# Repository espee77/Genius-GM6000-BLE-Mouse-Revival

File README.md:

# Reviving a Classic: Genius GM-6000 Wireless BLE / Wired USB / Air Mouse Conversion

This project is an open-source hardware and firmware conversion for the classic Genius GM-6000 mechanical ball mouse.

## History

Introduced in the late 1980s, the Genius GM-6000 was one of the flagship serial mice from [KYE Systems](https://www.geniusnet.com/en) under its Genius brand. At a time when the computer mouse was becoming an essential PC peripheral, the [Genius GM-6000](http://www.tcocd.de/Pictures/Peripheral/Genius/Genius.shtml) stood out with its robust optomechanical design, dynamic resolution technology, and support for both Microsoft and Mouse Systems serial protocols. Bundled with graphics software including Menu Maker and Dr. Halo/Dr. Genius, it was marketed as a premium mouse for both business and graphics applications.

By 1989, Genius advertisements described the company as "the largest selling mouse in Europe," with the GM-6000 featured prominently in its international marketing campaigns. Contemporary reviews also praised the mouse for its accuracy, compatibility, and comprehensive software bundle.

More than three decades later, the GM-6000 is still appreciated by collectors and retro-computing enthusiasts for its solid construction and durable mechanical tracking system. This project preserves those original mechanics while replacing the obsolete electronics with modern Bluetooth Low Energy technology, a rechargeable battery, and optional Air Mouse functionality.

---

## The Goal

The goal of this project is to preserve the look, feel, and mechanics of the original Genius GM-6000 while replacing its obsolete electronics with a modern Bluetooth Low Energy (BLE) system and adding Air Mouse functionality.

Instead of replacing the original ball mechanism with a modern optical sensor, this project preserves the original encoder wheels and tracking mechanics. A custom infrared optical detection system using IR LEDs and phototransistors reads the original quadrature encoders, maintaining the unique feel and behavior of the original mouse.

At the heart of the conversion is a custom PCB based on the [**Seeed Studio XIAO nRF52840 Sense**](https://wiki.seeedstudio.com/XIAO_BLE/), providing Bluetooth LE connectivity, rechargeable Li-Po battery support, intelligent power management, and modern firmware—all while fitting completely inside the original mouse shell.

If this project inspires someone to restore vintage hardware, learn electronics, or build an even better version, then it has already achieved its goal. Contributions, suggestions, forks, and improvements are always welcome.

---

# Project Goals

* Preserve the original appearance of the mouse
* Preserve the original ball and encoder mechanics
* Replace the original electronics with a modern custom PCB
* Add wireless Bluetooth Low Energy (BLE) connectivity
* Integrate a rechargeable Li-Po battery
* Keep both hardware and firmware fully open source

---

# Features

## Ball Mouse

* Bluetooth Low Energy (BLE) HID and wired USB HID support
* Original mechanical ball tracking
* Original infrared quadrature encoder system
* Adjustable cursor speed
* Three original mouse buttons
* Hold the middle button while moving the mouse to scroll smoothly
* Independent sensitivity settings for BLE and USB modes

## Air Mouse

* Automatic Air Mouse mode in both BLE and USB operation
* Automatic switching based on mouse orientation
* Motion smoothing, tremor reduction, and spike filtering
* Full button support while in Air Mouse mode

## Bluetooth

* Compatible with Windows, macOS, Linux, Android, and iPadOS
* Automatic BLE reconnection
* Bluetooth Battery Service (battery level reporting)
* Optimized BLE connection parameters for responsive cursor movement

## Power Management

* Rechargeable Li-Po battery
* Intelligent multi-stage power management
* Automatic IR LED power control
* Light Sleep and Deep Sleep modes for maximum battery life
* Automatic wake-up from movement, IMU motion (during Light Sleep), or button press (from Deep Sleep)

## Hardware

* Custom PCB designed specifically for the GM-6000
* Based on the Seeed Studio XIAO nRF52840 Sense
* Preserves the original buttons and tracking hardware
* Compact design that fits completely inside the original enclosure

---

# Using the Mouse

Despite its modern electronics, the converted GM-6000 is designed to preserve the familiar feel of the original mouse while adding modern wireless features and intelligent power management.

## Ball Mouse

The original mechanical ball, encoder wheels, and tracking mechanism are fully preserved. Cursor movement is generated from the original quadrature encoders, maintaining the characteristic feel of the original GM-6000.

## Scrolling

Since the original mouse has no scroll wheel, scrolling is performed by holding the **middle mouse button** while moving the mouse forward or backward. This allows smooth scrolling without altering the mouse's original appearance.

## Air Mouse

Rotating the mouse onto its side automatically activates **Air Mouse Mode**. The built-in IMU controls the cursor, making the mouse suitable for presentations or media control.

Switching between Ball Mouse and Air Mouse modes is completely automatic—no switches or software are required.

## USB & Bluetooth

The mouse operates as both a wired USB mouse and a Bluetooth Low Energy mouse. Connecting a USB cable automatically enables wired operation, while disconnecting it returns the mouse to Bluetooth mode.

## Intelligent Sleep Modes

To maximize battery life, the firmware automatically manages power consumption.

| Mode | Description |
|------|-------------|
| **Active** | Full performance while the mouse is in use. |
| **Light Sleep** | Infrared tracking is powered down while remaining ready to wake almost instantly. |
| **Deep Sleep** | Bluetooth disconnects and the mouse enters its lowest power state. |

The mouse automatically wakes from movement, IMU motion (during Light Sleep), or a button press (from Deep Sleep).

## Battery

Battery level is continuously monitored and reported through the Bluetooth Battery Service, allowing supported operating systems to display the remaining battery percentage.

## Factory Reset

If you experience Bluetooth pairing or connection problems, the firmware includes a built-in **Factory Reset** function.

With the mouse powered off, press and hold the **left**, **middle**, and **right** mouse buttons simultaneously while turning the mouse on. Keep all three buttons pressed for approximately **5 seconds** until the status LEDs indicate that the reset has started. The mouse will erase all stored Bluetooth pairing information, saved settings, usage statistics, battery statistics, and internal storage before automatically rebooting.

After a Factory Reset, remove the mouse from your computer's Bluetooth device list (if previously paired) and pair it again as a new device.

---

# Repository Contents

* [Firmware Installation Manual](Firmware%20installation%20manual.md)
* [Bill of material](https://github.com/espee77/Genius-GM6000-BLE-Mouse-Revival/blob/main/V1.0/Bill%20of%20Materials%20(BOM))
* [KiCad 10 project files](https://github.com/espee77/Genius-GM6000-BLE-Mouse-Revival/tree/main/V1.0/KICAD)
* [Schematics](https://github.com/espee77/Genius-GM6000-BLE-Mouse-Revival/tree/main/V1.0/Schematic)
* [Datasheets](https://github.com/espee77/Genius-GM6000-BLE-Mouse-Revival/tree/main/V1.0/Datasheets)
* [Firmware source code](https://github.com/espee77/Genius-GM6000-BLE-Mouse-Revival/tree/main/V1.01/Firmware)
* [JLCPCB zip file for board ordering](https://github.com/espee77/Genius-GM6000-BLE-Mouse-Revival/tree/main/V1.0/JLCPCB)
* [3D CAD files](https://github.com/espee77/Genius-GM6000-BLE-Mouse-Revival/tree/main/V1.0/3D%20files/Step214)
* [Pictures with assembly notes](https://github.com/espee77/Genius-GM6000-BLE-Mouse-Revival/tree/main/V1.0/Pictures%20with%20assembly%20notes)

---

# Why Open Source?

This project started as a fun way to combine retro hardware with modern electronics while preserving a classic piece of computer history.

By making both the hardware and firmware open source, I hope others can learn from it, improve the design, or use it as the foundation for their own retro hardware projects.

Contributions are always welcome, whether they involve hardware improvements, firmware development, documentation, testing, or entirely new ideas.

---

# Current Status

- **[V1.0 – Stable Release](https://github.com/espee77/Genius-GM6000-BLE-Mouse-Revival/tree/main/V1.01)**
- Second-generation custom PCB completed
- Stable Bluetooth Low Energy (BLE) HID firmware
- Reliable deep-sleep wake and automatic BLE reconnection
- Ball Mouse mode fully functional
- Air Mouse mode fully functional
- USB wired mouse mode implemented
- Battery monitoring and charging support
- Automatic power management with multi-stage sleep modes
- Built-in Factory Reset and diagnostic tools
- Extensively tested in daily use
- Optimized Bluetooth performance, responsiveness, and power consumption

---

# Disclaimers

* This is an experimental hobby project.
* Use the provided files and information entirely at your own risk.
* Li-Po batteries and electronic modifications can be hazardous if handled improperly. Always follow appropriate safety precautions.
* This hardware will not fit the Genius GM-6 which differs slightly from the GM-6000 (encoder positions, contact roller size, and rear switch).

---

# Acknowledgements

This project is an independent, community-created restoration effort. The CAD models were created by measuring an original Genius GM-6000 mouse and are not based on or derived from original manufacturer CAD data. "Genius" is a trademark of its respective owner and is used solely to identify the compatible product.
Special thanks to the retro hardware, maker, and open-source communities whose shared knowledge, documentation, and projects made this conversion possible.

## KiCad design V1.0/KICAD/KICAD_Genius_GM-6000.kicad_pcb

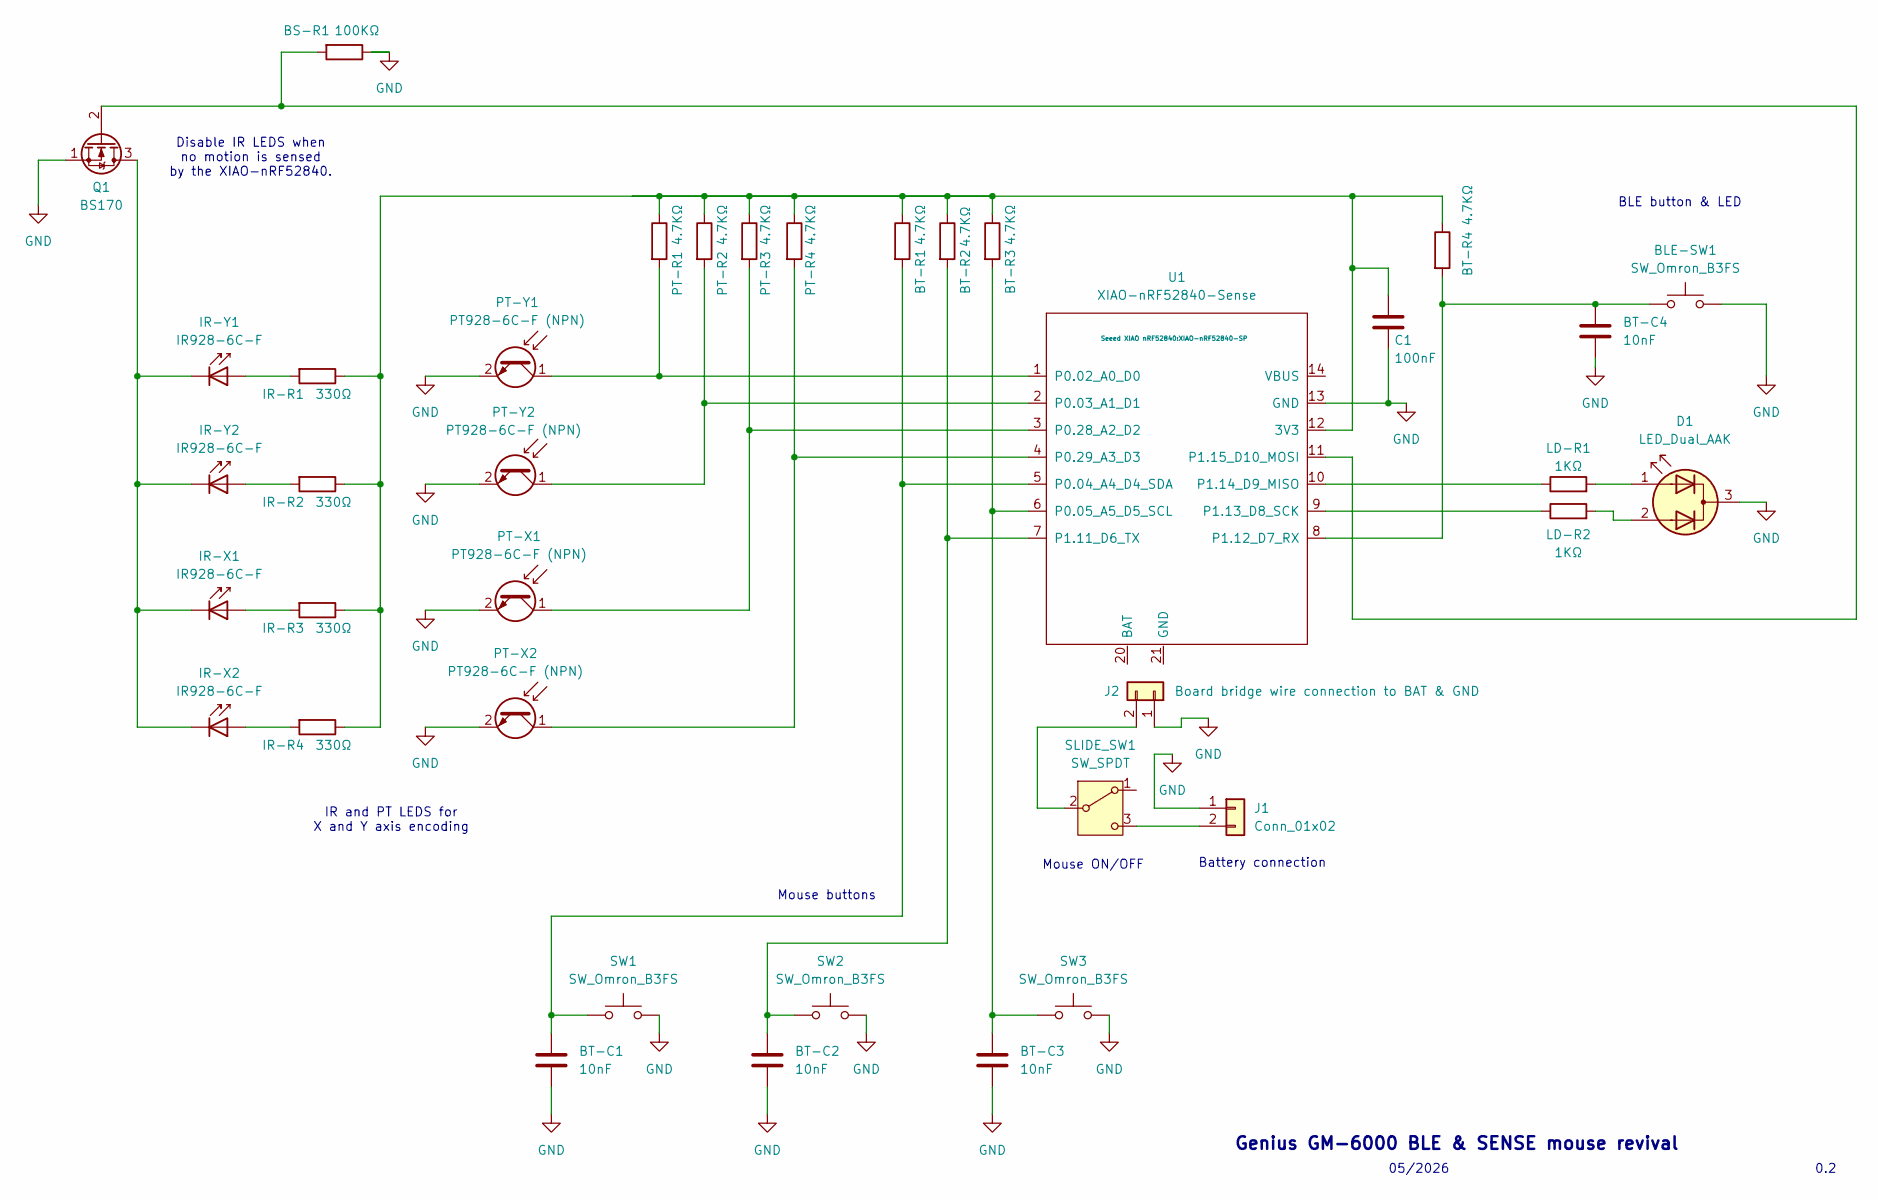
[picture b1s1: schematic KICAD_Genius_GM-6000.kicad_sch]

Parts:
BLE-SW1: SW_Omron_B3FS; SW_PUSH_6mm
BS-R1: 100KΩ; R_Axial_DIN0207_L6.3mm_D2.5mm_P7.62mm_Horizontal
BT-C1, BT-C2, BT-C3, BT-C4: 10nF; C_Disc_D5.0mm_W2.5mm_P2.50mm
BT-R1, BT-R2, BT-R3, BT-R4: 4.7KΩ; R_Axial_DIN0207_L6.3mm_D2.5mm_P7.62mm_Horizontal
C1: 100nF; C_Disc_D5.0mm_W2.5mm_P2.50mm
D1: LED_Dual_AAK; LED_D3.0mm-3
IR-R1, IR-R2, IR-R3, IR-R4: 330Ω; R_Axial_DIN0207_L6.3mm_D2.5mm_P7.62mm_Horizontal
IR-X1, IR-X2: IR928-6C-F; LED_SideEmitter_Rectangular_W4.5mm_H1.6mm
IR-Y1, IR-Y2: IR928-6C-F; LED_SideEmitter_Rectangular_W4.5mm_H1.6mm
J1: Conn_01x02
J2: Board bridge wire connection to BAT & GND; PinHeader_1x02_P2.54mm_Vertical
LD-R1, LD-R2: 1KΩ; R_Axial_DIN0207_L6.3mm_D2.5mm_P7.62mm_Horizontal
PT-R1, PT-R2, PT-R3, PT-R4: 4.7KΩ; R_Axial_DIN0207_L6.3mm_D2.5mm_P7.62mm_Horizontal
PT-X1, PT-X2: PT928-6C-F (NPN); Osram_LPT80A
PT-Y1, PT-Y2: PT928-6C-F (NPN); Osram_LPT80A
Q1: BS170; TO-92L_Inline_Wide
SLIDE_SW1: SW_SPDT; SW_Slide_SPDT_Straight_CK_OS102011MS2Q
SW1, SW2, SW3: SW_Omron_B3FS; SW_PUSH_6mm
U1: XIAO-nRF52840-Sense; XIAO-nRF52840-SP

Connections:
GND: BLE-SW1.2, BS-R1.1, BT-C1.2, BT-C2.2, BT-C3.2, BT-C4.2, C1.2, D1.3 (K), J1.1, J2.1, PT-X1.2 (E), PT-X2.2 (E), PT-Y1.2 (E), PT-Y2.2 (E), Q1.1 (S), SW1.2, SW2.2, SW3.2, U1.13 (GND)
unnamed: D1.1 (A1), LD-R1.2
unnamed: D1.2 (A2), LD-R2.2
unnamed: IR-R3.2, IR-X1.2 (A)
unnamed: IR-X1.1 (K), IR-X2.1 (K), IR-Y1.1 (K), IR-Y2.1 (K), Q1.3 (D)
unnamed: IR-R4.2, IR-X2.2 (A)
unnamed: IR-R1.2, IR-Y1.2 (A)
unnamed: IR-R2.2, IR-Y2.2 (A)
unnamed: J1.2, SLIDE_SW1.3 (C)
unnamed: J2.2, SLIDE_SW1.2 (B)
unnamed: PT-R3.2, PT-X1.1 (C), U1.3 (P0.28_A2_D2)
unnamed: PT-R4.2, PT-X2.1 (C), U1.4 (P0.29_A3_D3)
unnamed: PT-R1.2, PT-Y1.1 (C), U1.1 (P0.02_A0_D0)
unnamed: PT-R2.2, PT-Y2.1 (C), U1.2 (P0.03_A1_D1)
unnamed: BS-R1.2, Q1.2 (G), U1.11 (P1.15_D10_MOSI)
unnamed: BT-R1.1, BT-R2.1, BT-R3.1, BT-R4.1, C1.1, IR-R1.1, IR-R2.1, IR-R3.1, IR-R4.1, PT-R1.1, PT-R2.1, PT-R3.1, PT-R4.1, U1.12 (3V3)
unnamed: BT-C1.1, BT-R1.2, SW1.1, U1.5 (P0.04_A4_D4_SDA)
unnamed: BT-C3.1, BT-R3.2, SW3.1, U1.6 (P0.05_A5_D5_SCL)
unnamed: BT-C2.1, BT-R2.2, SW2.1, U1.7 (P1.11_D6_TX)
unnamed: BLE-SW1.1, BT-C4.1, BT-R4.2, U1.8 (P1.12_D7_RX)
unnamed: LD-R2.1, U1.9 (P1.13_D8_SCK)
unnamed: LD-R1.1, U1.10 (P1.14_D9_MISO)

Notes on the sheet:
0.2
Battery connection
Mouse buttons
IR and PT LEDS for X and Y axis encoding
05/2026
Mouse ON/OFF
Genius GM-6000 BLE & SENSE mouse revival
Disable IR LEDS when no motion is sensed by the XIAO-nRF52840.
BLE button & LED

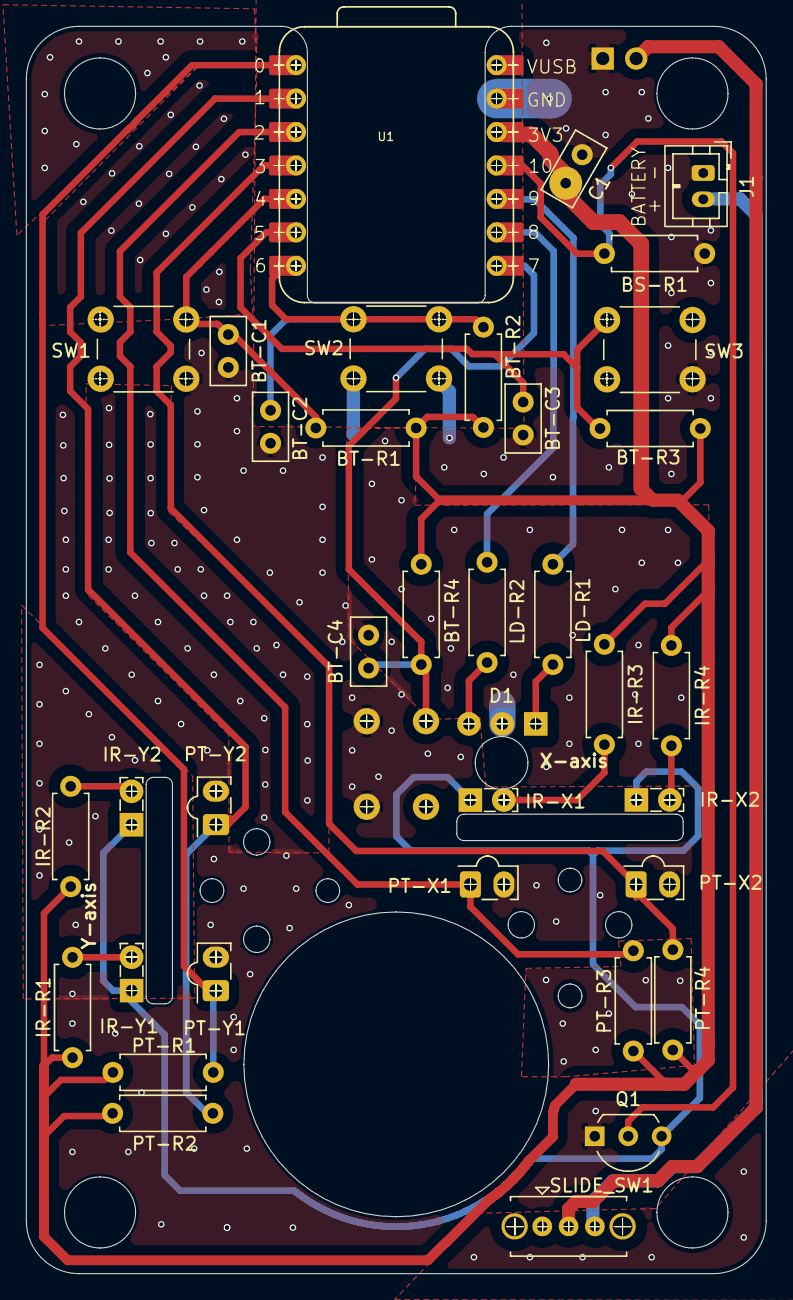
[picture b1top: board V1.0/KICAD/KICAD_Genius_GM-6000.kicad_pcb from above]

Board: 2 copper layers, 56.2 x 94.8 mm, 38 parts (1 on the bottom side), 22 nets.

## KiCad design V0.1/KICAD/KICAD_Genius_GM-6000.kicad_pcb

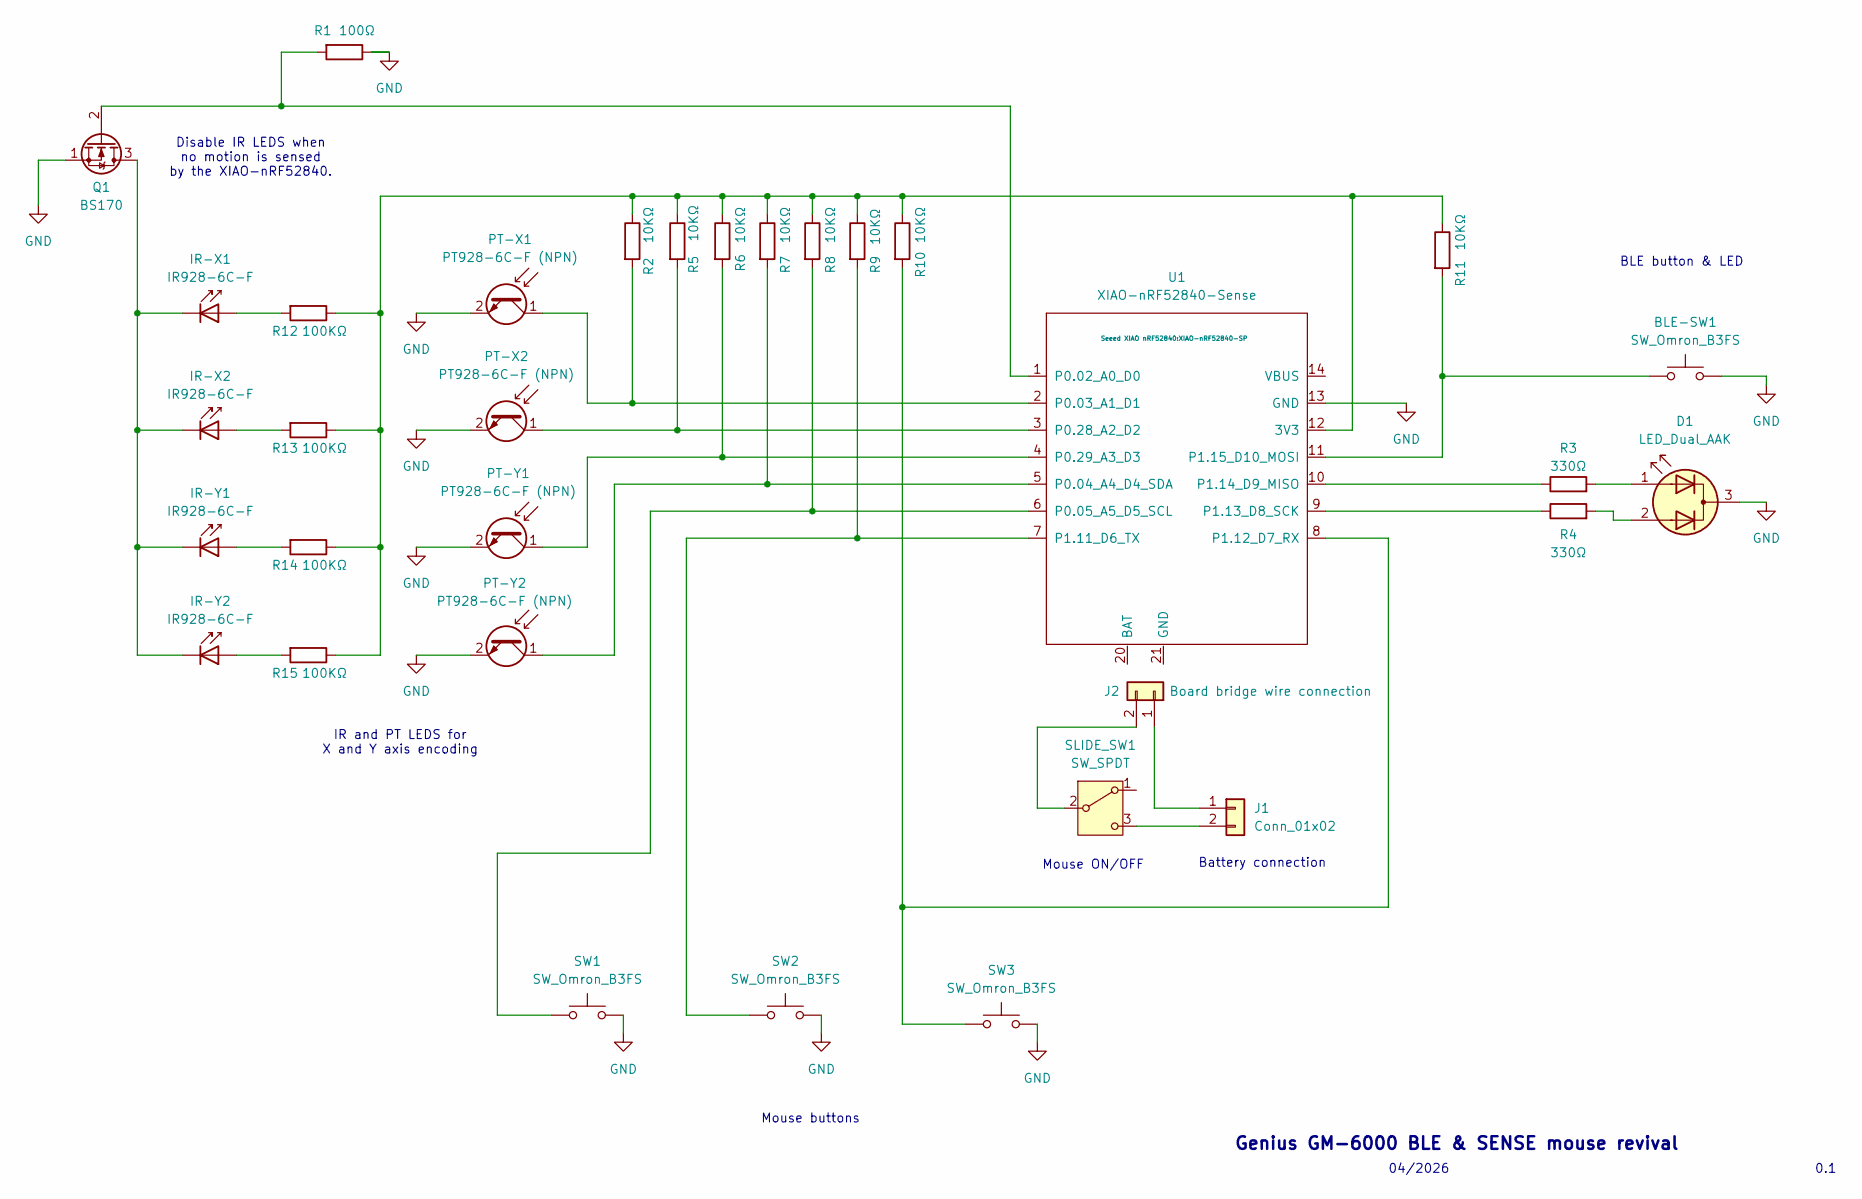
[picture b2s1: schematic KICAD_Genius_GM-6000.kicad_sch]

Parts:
BLE-SW1: SW_Omron_B3FS; SW_PUSH_6mm
D1: LED_Dual_AAK; LED_D3.0mm-3
IR-X1, IR-X2: IR928-6C-F; LED_SideEmitter_Rectangular_W4.5mm_H1.6mm
IR-Y1, IR-Y2: IR928-6C-F; LED_SideEmitter_Rectangular_W4.5mm_H1.6mm
J1: Conn_01x02
J2: Board bridge wire connection; PinHeader_1x02_P2.54mm_Vertical
PT-X1, PT-X2: PT928-6C-F (NPN); Osram_LPT80A
PT-Y1, PT-Y2: PT928-6C-F (NPN); Osram_LPT80A
Q1: BS170; TO-92_Inline
R1: 100Ω; R_Axial_DIN0207_L6.3mm_D2.5mm_P7.62mm_Horizontal
R2, R5, R6, R7, R8, R9, R10, R11: 10KΩ; R_Axial_DIN0207_L6.3mm_D2.5mm_P7.62mm_Horizontal
R3, R4: 330Ω; R_Axial_DIN0207_L6.3mm_D2.5mm_P7.62mm_Horizontal
R12, R13, R14, R15: 100KΩ; R_Axial_DIN0207_L6.3mm_D2.5mm_P7.62mm_Horizontal
SLIDE_SW1: SW_SPDT; SW_Slide_SPDT_Straight_CK_OS102011MS2Q
SW1, SW2, SW3: SW_Omron_B3FS; SW_PUSH_6mm
U1: XIAO-nRF52840-Sense; XIAO-nRF52840-SP

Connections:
GND: BLE-SW1.2, D1.3 (K), PT-X1.2 (E), PT-X2.2 (E), PT-Y1.2 (E), PT-Y2.2 (E), Q1.1 (S), R1.1, SW1.2, SW2.2, SW3.2, U1.13 (GND)
unnamed: D1.1 (A1), R3.2
unnamed: D1.2 (A2), R4.2
unnamed: IR-X1.2 (A), R12.2
unnamed: IR-X1.1 (K), IR-X2.1 (K), IR-Y1.1 (K), IR-Y2.1 (K), Q1.3 (D)
unnamed: IR-X2.2 (A), R13.2
unnamed: IR-Y1.2 (A), R14.2
unnamed: IR-Y2.2 (A), R15.2
unnamed: J1.1, J2.1
unnamed: J1.2, SLIDE_SW1.3 (C)
unnamed: J2.2, SLIDE_SW1.2 (B)
unnamed: PT-X1.1 (C), R2.2, U1.2 (P0.03_A1_D1)
unnamed: PT-X2.1 (C), R5.2, U1.3 (P0.28_A2_D2)
unnamed: PT-Y1.1 (C), R6.2, U1.4 (P0.29_A3_D3)
unnamed: PT-Y2.1 (C), R7.2, U1.5 (P0.04_A4_D4_SDA)
unnamed: Q1.2 (G), R1.2, U1.1 (P0.02_A0_D0)
unnamed: R2.1, R5.1, R6.1, R7.1, R8.1, R9.1, R10.1, R11.1, R12.1, R13.1, R14.1, R15.1, U1.12 (3V3)
unnamed: R8.2, SW1.1, U1.6 (P0.05_A5_D5_SCL)
unnamed: R9.2, SW2.1, U1.7 (P1.11_D6_TX)
unnamed: R10.2, SW3.1, U1.8 (P1.12_D7_RX)
unnamed: R4.1, U1.9 (P1.13_D8_SCK)
unnamed: R3.1, U1.10 (P1.14_D9_MISO)
unnamed: BLE-SW1.1, R11.2, U1.11 (P1.15_D10_MOSI)

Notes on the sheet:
0.1
Battery connection
Mouse buttons
IR and PT LEDS for X and Y axis encoding
04/2026
Mouse ON/OFF
Genius GM-6000 BLE & SENSE mouse revival
Disable IR LEDS when no motion is sensed by the XIAO-nRF52840.
BLE button & LED

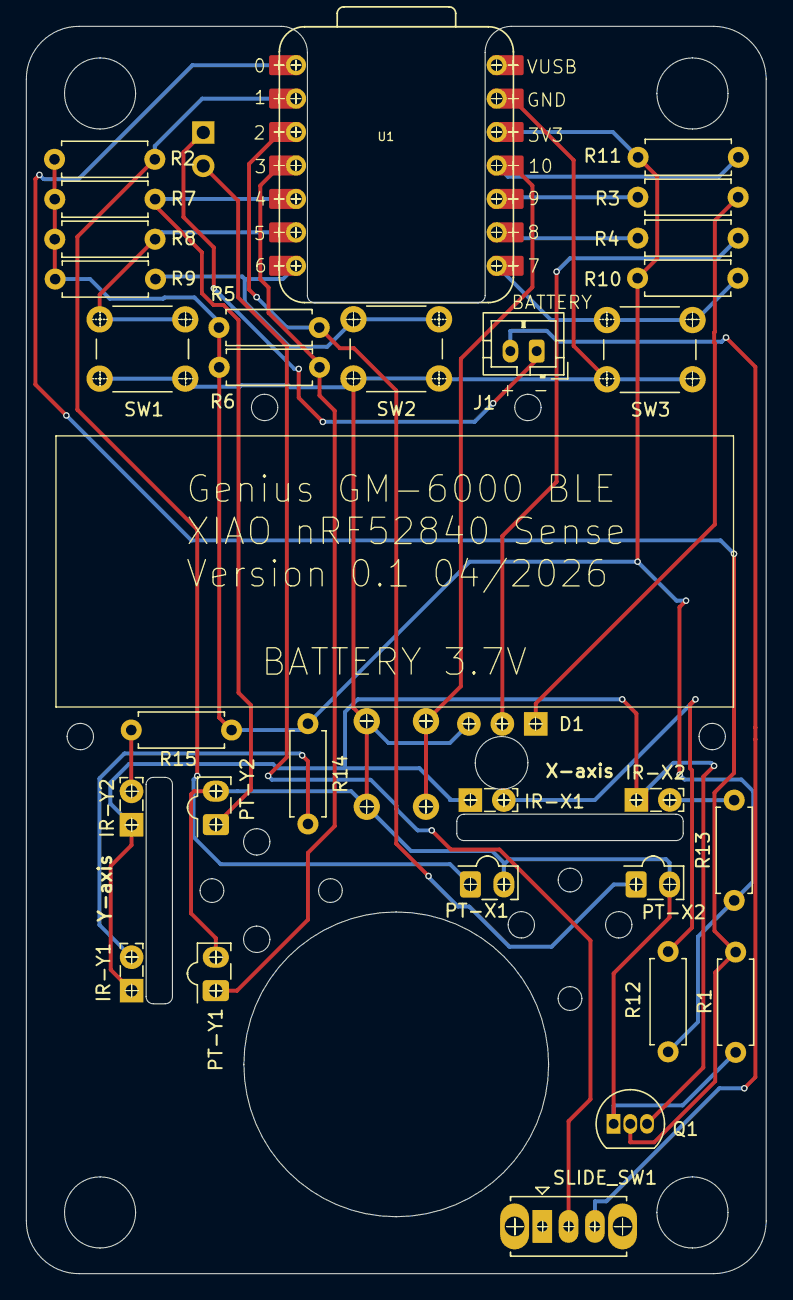
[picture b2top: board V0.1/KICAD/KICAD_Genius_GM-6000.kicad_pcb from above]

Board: 2 copper layers, 56.2 x 94.8 mm, 33 parts (1 on the bottom side), 23 nets.

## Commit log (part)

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2026-05-10 First upload
    Unfinished work V0.1 status
2026-05-10 Revise README with project details and goals
    Updated the README to provide detailed project information and goals for the Genius GM-6000 BLE Mouse Revival.
2026-05-10 Replace images in README with updated versions
    Updated images in README to showcase the Genius GM-6000 mouse.
2026-05-10 Standardize image sizes in README.md
    Updated image tags to use a consistent width of 800 pixels.
2026-05-10 Revise README for project goals and features
    Updated project goals and features sections for clarity and consistency.
2026-05-10 Revise README for project goals and features
    Updated README to reflect changes in project details and features.
2026-05-10 Fix grammar in README disclaimers
    Corrected grammatical errors in the disclaimers section.
2026-05-10 Revise README with project details and goals
    Updated project description and goals in README.
2026-05-10 Update README for clarity and emphasis
    Emphasized project success criteria and improved contribution wording.
2026-05-10 Encourage contributions and project improvements
    Added a note encouraging contributions and learning from the project.
2026-06-27 Revise README for Genius GM-6000 BLE conversion
    Updated project description and goals for clarity and detail.
2026-06-27 Refactor README formatting and remove extra lines
    Removed redundant line breaks and adjusted formatting.
